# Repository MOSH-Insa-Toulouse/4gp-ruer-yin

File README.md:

# 22-23 4gp-ruer-yin

Ce projet s'inscrit dans l'UF **"I4GPMH21 - du capteur au banc de test en open source hardware"** en 4eme année département d'INSA Toulouse.
***

Ce projet sert à caractériser la résistance des capteurs graphites sous différentes conditions de déformation. Une application de déformation change la distance moyenne des particules de graphite. En effet, la conductivité de la couche graphite dépende vachement de cette distance moyenne et donc la déformation. En pratique, on applique un contraint et déposer le capteur sur les semis sphères pour caractériser les diffèrent déformation. L’ordre de grandeur de ce capteur est 100Mohm. Il n’est pas usuel. Par exemple il est hors la gamme de mesure des multimètres commerciaux. Donc il est essentiel dans ce projet de planifier et de fabriquer un circuit PCB qu’il nous permettre de mesurer cette résistance. De plus, il est aussi intéressant d’élaborer un système de communication pour communiquer les données avec notre téléphone Android avec Bluetooth. 
***  

## Table de matière
* [1. Liverables et matériels](#PremiereSection)
* [2. Simulation LTSPICE](#SixiemeSection)
* [3. Réalisation Kicad et PCB](#DeuxiemeSection)
* [4. Code Arduino](#TroisemeSection)
* [5. (Application MIT app inventor)](#QuartiemeSection)
* [6. (Banc de test)](#CinqiemeSection)
## 1. Liverables et matériels 
***
Les liverables principaux sont: 
* Un sheild PCB de module Arduino Uno au dessus on a intégré un circuit d'amplificateur, un OLED et un module Bluetooth.
* Un application Android exploré avec MIT app inventor. Cet app sert à communiquer en temp relle avec le module d'Arduino des valeurs de resistance et les afficher. 
* Un script d'Arduino permettant de calculer en temps relle du valeur de resistance, communiquer ce valeur avec l'application mentionné au dessus et l'afficher sur l'écran OLED
* Un datasheet contenant tous les caratérisation du capteur. 

Les matériels nécessaires sont:
* Un carte PCB de module Arduino Uno
* Un module Bluetooth HC-05
* Un écran OLED
* Un amplificateur opérationnel LTC1050  
* Deux condensateurs de 100 nF  
* Un condensateur de 100 µF 
* Deux résistances de 100 KOhms  
* Une résistance de 10 KOhms  
* Deux résistances de 1 KOhm  
* Un papier dessiné d'un trace de crayon imposé
## 2. Simulation LTSpice
La capteur graphite a une l'ordre de grandeur de 100MOhm. Le voltage maximun d'Arduino est 5V. Il est donc difficile de mesure la valeur de capteur si on n'arrive pas à amplifier la signal. On a donc designé un circuit d'amplification pour avoir un facteur 100 du signal. Ensuite on peut calculer le valeur précise de la résistance. Voici l'image du circuit de LTSpice:

## 3. Réalisation Kicad et PCB 
Pour designer un carte PCB où on peut intégrer les matériels mentionnés au dessus, il est nécessaire de utiliser kicad pour designer un circuit de conductant de cuivre et les composants soudés au dessus. Les détailes de ces composants et de la cirtuit sont visibles dans les images au dessous.  
* L'image des symboles:

* L'image du PCB et son image 3D

Après les vérifications electroniques, nous avons envoyé le fichier d'imprimant à Madame Catherine Crouzet pour poursuivre un impression de PCB avec elle. Ce PCB est réalisé sur un plaquette epoxy. A la fin des procédés de photolitographie et de gravure chimique, l'impression du circuit est réalisé sur l'un de cette plaquette. Nous avons poursuive les perçages des trous pour intégrer les matériels et le soudage de ces matériels. Les trous on les 2 différents diamètres. Pour les trous du module Arduino Uno, le diametre est 1mm. Les trous de reste ont de diametre 0.8mm selon la consigne de Madame Catherine Crouzet.

## 4. Code Arduino 
Les objetifs de script d'arduino nommé [plz-work.ino](https://github.com/MOSH-Insa-Toulouse/4gp-ruer-yin/tree/main/Arduino/plz-work/plz-work) sont:
* mesurer le voltage en temp relle de la sortie du circuit (VA0)
* En déduire la valeur de résistance R du capteur graphite.
* Envoyer la valeur de tension mesuré sous 1 octect par le module de bluetooth.
* Afficher la valeur de résistance sur l'écran OLED.
Le code essentielle est effctivement les code de mesure et de calcule de valeur de résistance. Selon les simulations de LTSpice, on peut en deduit la resistance exact que nous aimerions de mesurer.

## 5. Application (MIT app inventor) 
Les objetifs de cet application est de communiquer en temp relle avec le module d'Arduino des valeurs de resistance et les afficher. 
La connection de bluetooth se réalise par trois bloc de "when". On affiche le liste d'adresse de bluetooth dans le mémoire de téléphone. Puis on pourra sélectionner un adresse. Le téléphone est ensuite connecté à bluetooth. 

Le Bouton "Reception_bluetooth" sert à lancer le chronologe. Ensuite, l'application fait le calcule depuis un octet envoyé par le Bluetooth HC-05 en utilisant la simulation de LTspice. Dans le graphe, on trace le graphe en tracant tous les lignes entre tous les 2 point.   

## 6. Banc de test 

Nous avons testé notre capteur graphite dans les différent angle de déformation. Ce dernier est caractériser par un banc de test dans l'image au dessus. Le banc de test est composé par les différents semi sphère de diamètre 5cm, 4.5cm, 4cm, 3.5cm, 3cm, 2.5cm, 2cm. Pendant le test, on colle le côté où il y a pas de graphite aux différent semi shère du banc de test et on fait le mesure du résistance. Ensuite on cherche la relation entre le déformation définit comme par le formule ε=D/(2*R)(où ε est la déformation, D est l'épaisseur du papier, R est la rayon de courbure) et la variation relative de (ΔR/R0).  
Nous avons décidé de faire les tests sur un graphite de 2H en applicant la seulement la tension. Il y a pas de mesure sous condition de compression car on a réalisé pendant les mesure que la forme de capteur graphite n'est pas réversible. Premièrement, on peut très facilement dépasser le limite élastique du papier. Deuxièmement, même si on ne change pas la forme de ce papier, la résistance n'est souvent pas réversible. En conséquence, on a choisit de faire le mesure seulment sur la tension pour chaque échantillon. Les résultat sont montré dans le fichier Datasheet.pdf.
Le résultat montre une relation linéaire entre la déformation et la variation relative de la résistance de capteur. On peut déduit l'angle de déformation  depuis un résistance mesurée.

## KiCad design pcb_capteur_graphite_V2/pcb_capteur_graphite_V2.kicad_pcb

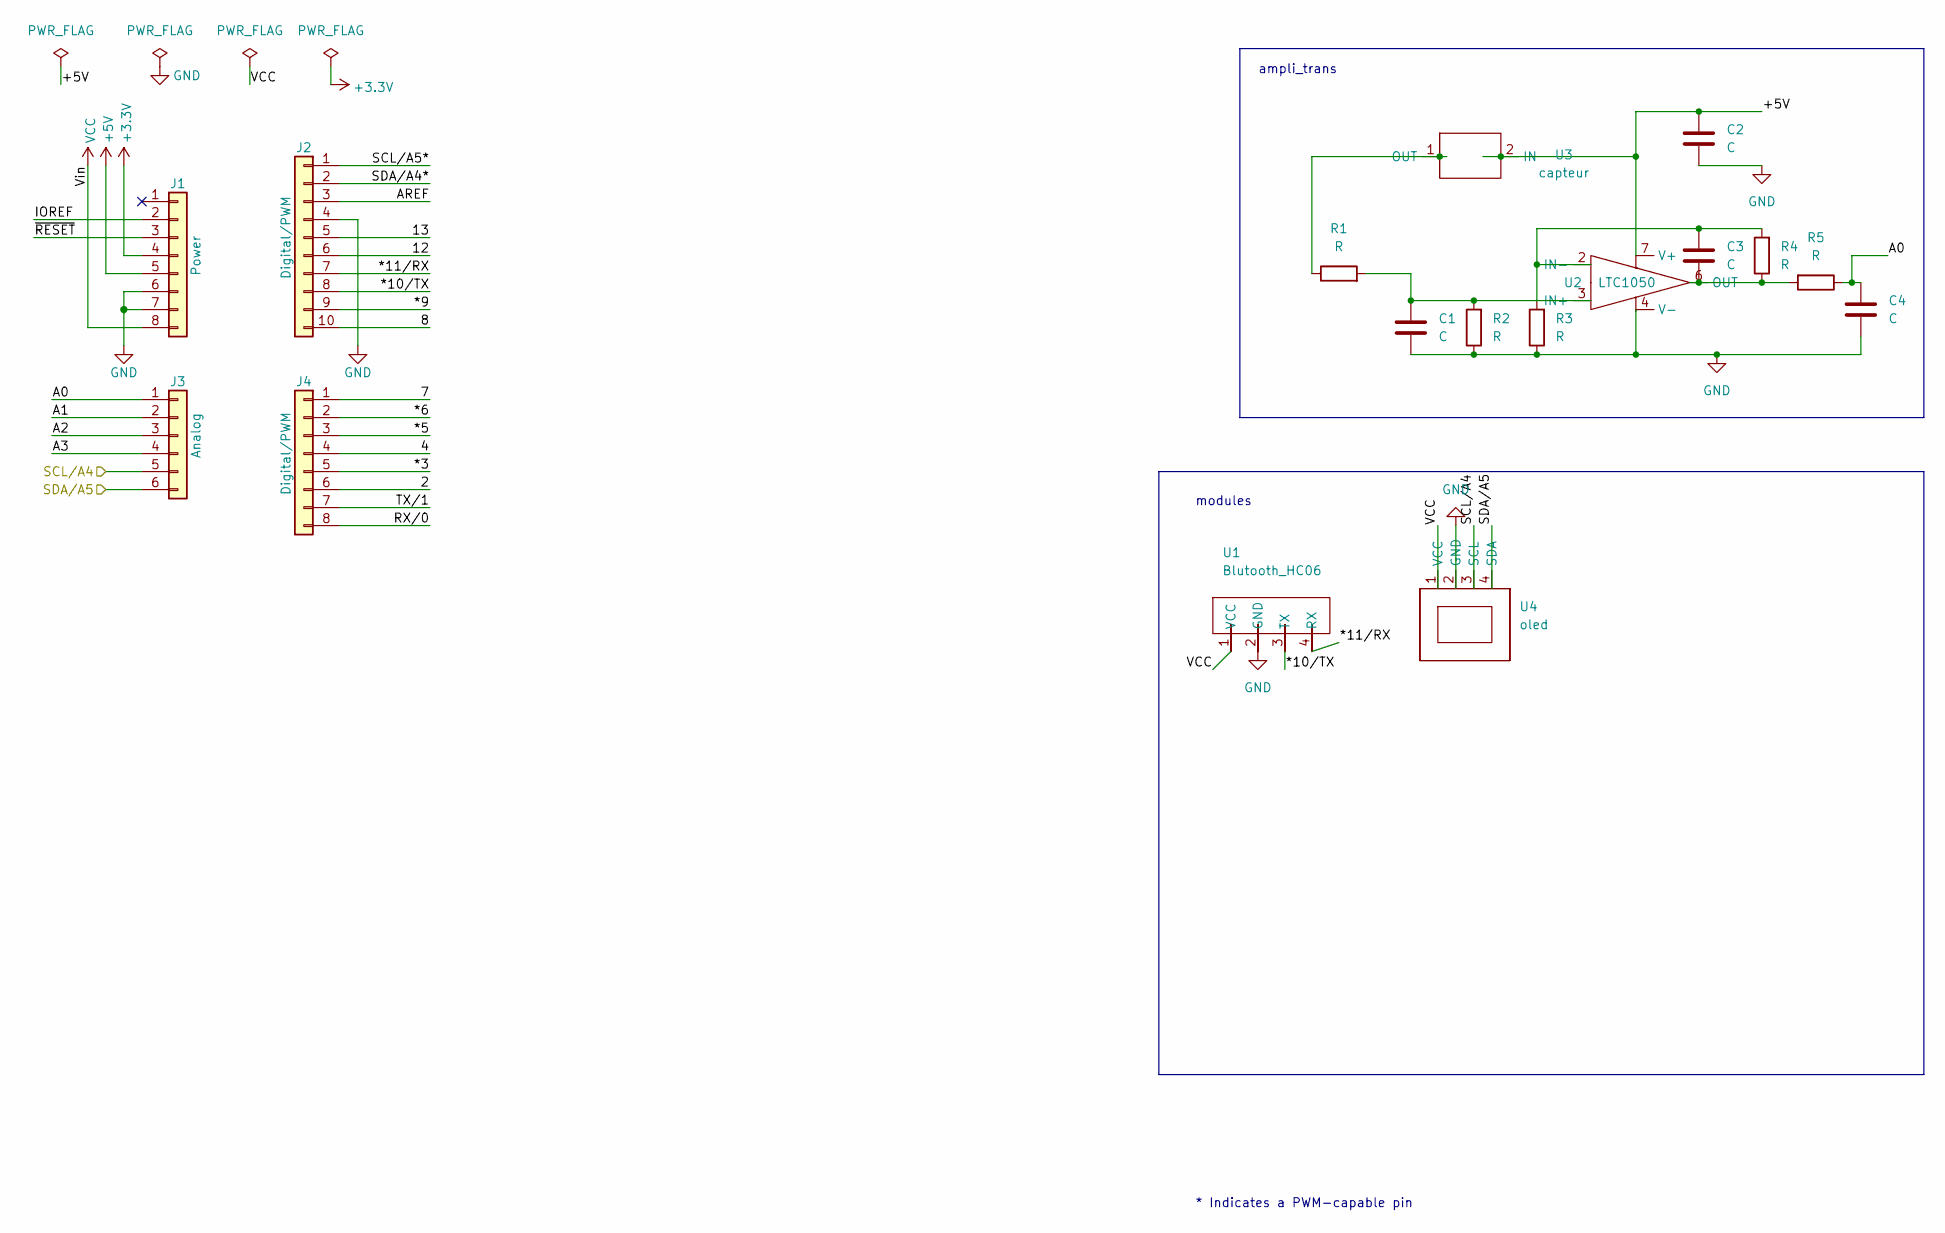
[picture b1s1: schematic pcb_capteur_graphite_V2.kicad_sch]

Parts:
C1, C2, C4: C; Conductance
C3: C; C_Rect_L7.0mm_W4.5mm_P5.00mm
J1: Power; PinSocket_1x08_P2.54mm_Vertical
J2: Digital/PWM; PinSocket_1x10_P2.54mm_Vertical
J3: Analog; PinSocket_1x06_P2.54mm_Vertical
J4: Digital/PWM; PinSocket_1x08_P2.54mm_Vertical
R1, R2, R3, R4, R5: R; Resistor
U1: Blutooth_HC06; Bluetooth
U2: LTC1050; DIP-8_W7.62mm
U3: capteur
U4: oled; OLED

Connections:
+3V3: J1.4
+5V: C2.1, J1.5, U2.7 (V+), U3.2 (IN)
/2: J4.6
/4: J4.4
/7: J4.1
/8: J2.10
/12: J2.6
/13: J2.5
/*3: J4.5
/*5: J4.3
/*6: J4.2
/*9: J2.9
/*10/TX: J2.8, U1.3 (TX)
/*11/RX: J2.7, U1.4 (RX)
/A0: C4.1, J3.1, R5.1
/A1: J3.2
/A2: J3.3
/A3: J3.4
/AREF: J2.3
/IOREF: J1.2
/RX/0: J4.8
/SCL/A4: J3.5, U4.3 (SCL)
/SCL/A5*: J2.1
/SDA/A4*: J2.2
/SDA/A5: J3.6, U4.4 (SDA)
/TX/1: J4.7
/~RESET: J1.3
GND: C1.2, C2.2, C4.2, J1.6, J1.7, J2.4, R2.1, R3.1, U1.2 (GND), U2.4 (V-), U4.2 (GND)
unnamed: C1.1, R1.2, R2.2, U2.3 (IN+)
unnamed: C3.1, R3.2, R4.2, U2.2 (IN-)
unnamed: C3.2, R4.1, R5.2, U2.6 (OUT)
unnamed: R1.1, U3.1 (OUT)
VCC: J1.8, U1.1 (VCC), U4.1 (VCC)

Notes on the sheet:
ampli_trans
modules
* Indicates a PWM-capable pin

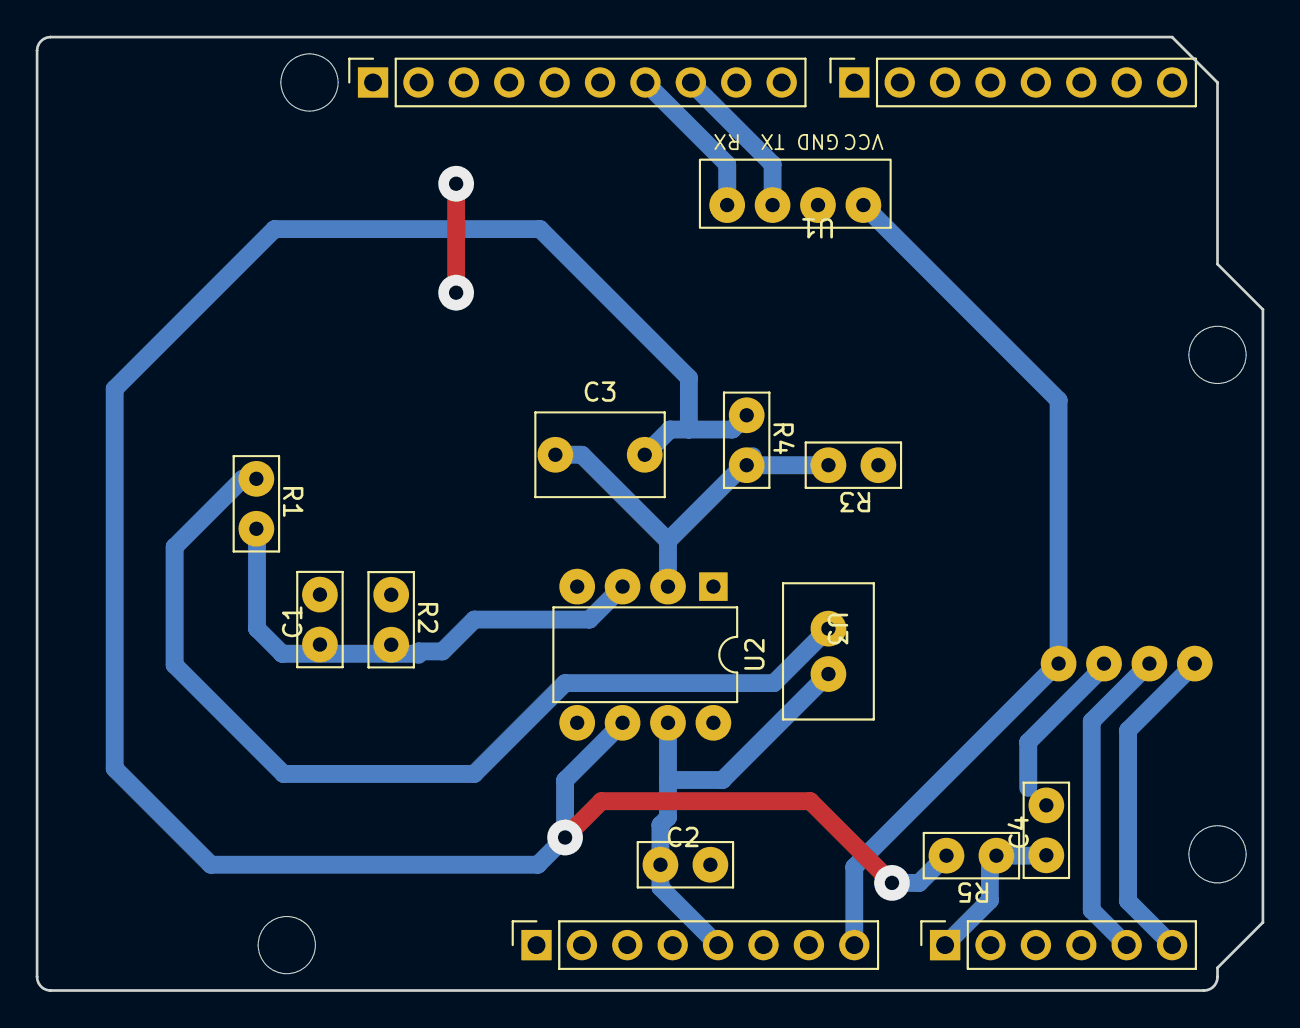
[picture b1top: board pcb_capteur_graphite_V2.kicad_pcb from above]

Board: 2 copper layers, 68.6 x 53.3 mm, 21 parts (1 on the bottom side), 12 nets.

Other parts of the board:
MH1, MH2, MH3, MH4: MountingHole_3.2mm

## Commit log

2023-03-14 gitignore added - pcb fini
2023-04-10 Code Arduino
2023-04-22 version de circuit imprimé
2023-05-10 Réorganisation fichier
2023-05-10 MAJ pcb
2023-05-10 code oled + capteur
2023-05-11 README
2023-05-11 ajout fichier aia
2023-05-11 LTSPICE
2023-05-12 MAJ oled
2023-05-13 what to say
2023-05-13 correction loop bluetooth
2023-05-14 add datasheet
2023-05-14 rename datasheet
2023-05-15 ajoute aia apk, images utiles et renouvelle plz
2023-05-15 plz peut envoyer les octets
2023-05-29 tous les images
2023-05-29 mise jour noms d'image readme
2023-05-29 manque d'image
2023-05-29 mise a jour image
2023-05-29 update datasheet
